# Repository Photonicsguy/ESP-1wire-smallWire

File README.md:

# ESP-1wire-smallWire
Small ESPHome module using an ESP-01M for 1wire sensors
- 1Wire bus protected by a polyfuse, with simple bus fault detection (1Wire bus power connected to GPIO3 after polyfuse)
- 1Wire bus IO is on GPIO03
- Mostly 0802 size SMD components

## Components
- ESP-01M
- DS18B20 1Wire temperature sensor
- 4x2 pin header (optional socket for ESP-01M)
   - Digikey: 732-61300821821-ND
- 100mA polyfuse
   - Digikey: 13-BK60-010-DZ-ND
- 3.3V Reg, HT7333-A, SOT89
   - Digikey: 4518-HT7333-ACT-ND
- 2x10K Resistor, 0802
- 4.7K Resistor, 0802
- 62 Ohm Resistor, 0802
- 10uF Capacitor, 4x4.5
- 479pF Capacitor, 0802
- JST Connectors or other connector of your choice
   - 2 pin for power
   - 3 pin for 1Wire

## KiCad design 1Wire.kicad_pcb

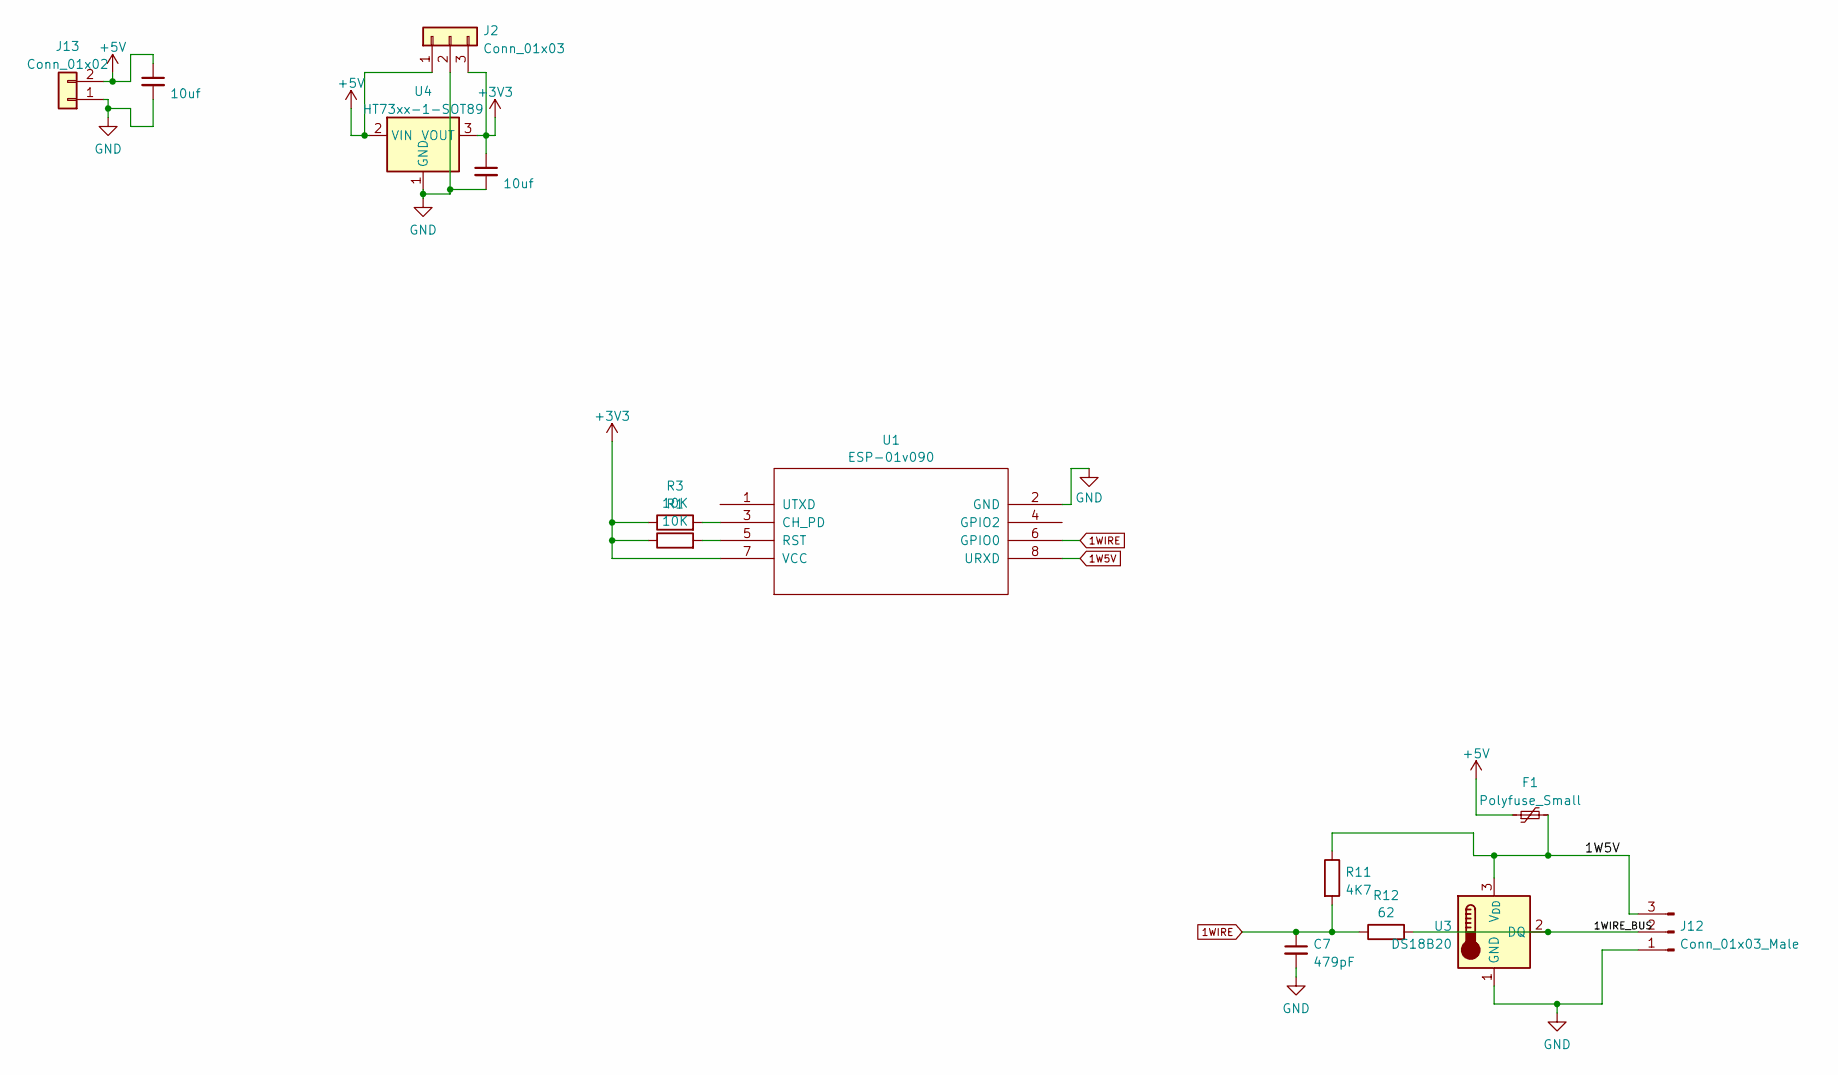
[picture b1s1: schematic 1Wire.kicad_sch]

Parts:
C1, C2: 10uf; CP_Elec_4x4.5; Part 732-8430-ND
C7: 479pF; C_0805_2012Metric
F1: Polyfuse_Small; R_Axial_DIN0204_L3.6mm_D1.6mm_P5.08mm_Vertical
J2: Conn_01x03; PinHeader_1x03_P2.54mm_Vertical
J12: Conn_01x03_Male; JST_XH_B3B-XH-A_1x03_P2.50mm_Vertical
J13: Conn_01x02; PinHeader_1x02_P2.54mm_Vertical
R1, R3: 10K; R_0805_2012Metric
R11: 4K7; R_0805_2012Metric
R12: 62; R_0805_2012Metric
U1: ESP-01v090; ESP-01
U3: DS18B20; TO-92_Inline
U4: HT73xx-1-SOT89; SOT-89-3

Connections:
1W5V: F1.2, J12.3, R11.1, U1.8 (URXD), U3.3 (V_{DD})
1WIRE: C7.1, R11.2, R12.1, U1.6 (GPIO0)
+3V3: C2.1, J2.3, R1.1, R3.1, U1.7 (VCC), U4.3 (VOUT)
+5V: C1.1, F1.1, J2.1, J13.2, U4.2 (VIN)
/1WIRE_BUS: J12.2, R12.2, U3.2 (DQ)
GND: C1.2, C2.2, C7.2, J2.2, J12.1, J13.1, U1.2 (GND), U3.1 (GND), U4.1 (GND)
unnamed: R3.2, U1.3 (CH_PD)
unnamed: R1.2, U1.5 (RST)

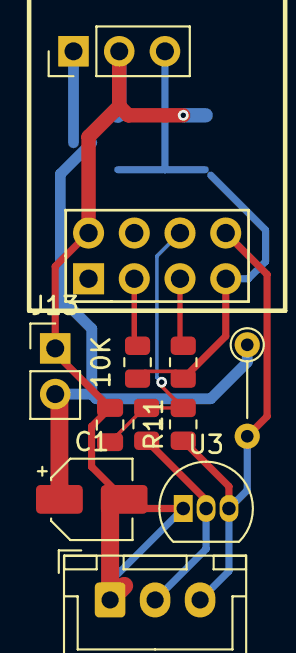
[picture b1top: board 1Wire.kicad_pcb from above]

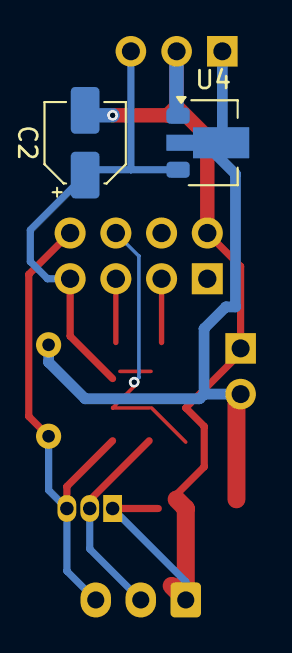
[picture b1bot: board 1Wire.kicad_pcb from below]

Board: 2 copper layers, 14 parts (2 on the bottom side), 8 nets.

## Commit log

2025-12-12 Create LICENSE
